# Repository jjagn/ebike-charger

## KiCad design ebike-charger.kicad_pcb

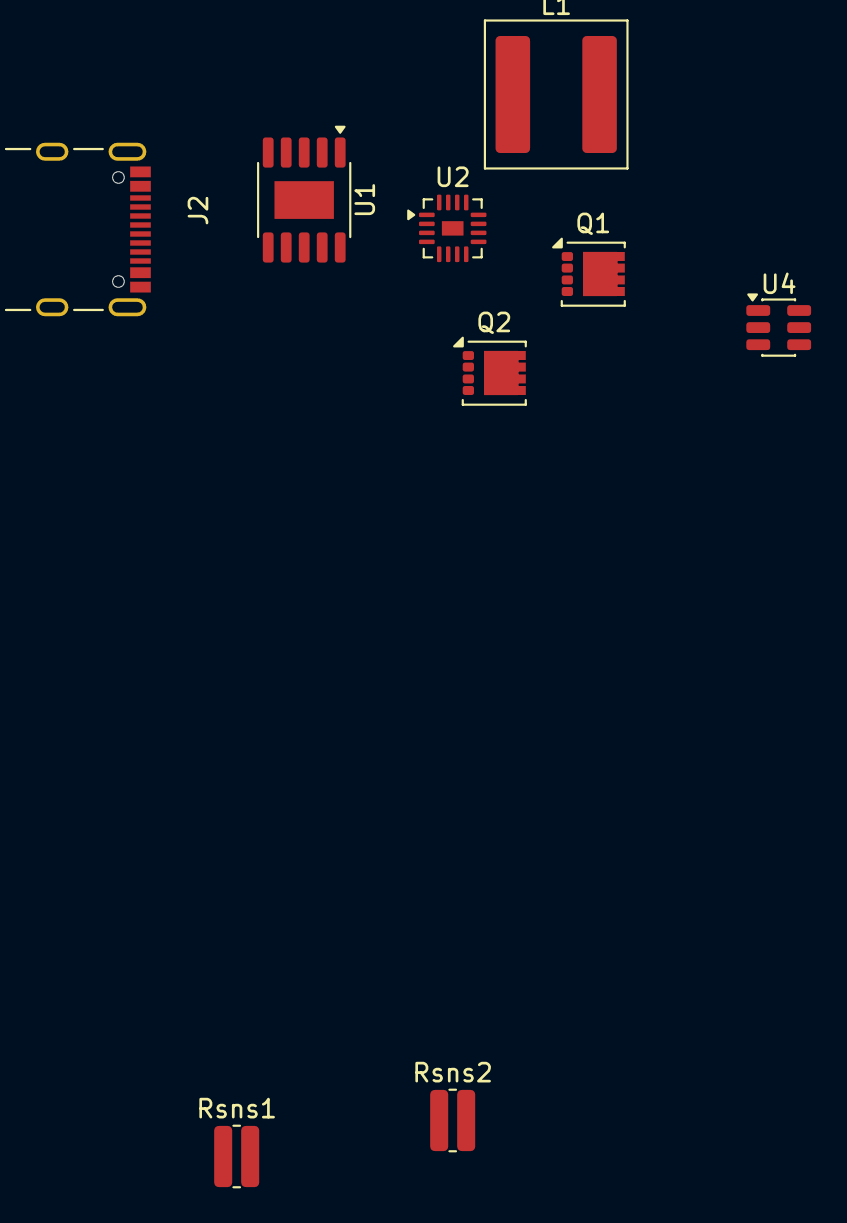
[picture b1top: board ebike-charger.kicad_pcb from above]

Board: 2 copper layers, 9 parts (0 on the bottom side), 12 nets, no tracks yet.

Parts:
J2: UJ20-C-H-G-SMT-2A-P16-TR; SAMESKY_UJ20-C-H-G-SMT-2A-P16-TR
L1: 8.2uH/14.5mR; L_Coilcraft_XAL7070-XXX
Q1, Q2: CSD18543Q3A; VSON-8_3.3x3.3mm_P0.65mm_NexFET
Rsns1, Rsns2: 8mR; R_0612_1632Metric
U1: CH224K; SSOP-10-1EP_3.9x4.9mm_P1mm_EP2.1x3.3mm
U2: TPS43060RTER; Texas_RTE_WQFN-16-1EP_3x3mm_P0.5mm_EP1.2x0.8mm
U4: LM74700; SOT-23-6

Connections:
/Boost Converter/HDRV: Q2.4 (G), U2.13 (HDRV)
/Boost Converter/LDRV: Q1.4 (G), U2.8 (LDRV)
/Boost Converter/SW: L1.2, Q1.5 (D), Q2.1 (S), Q2.2 (S), Q2.3 (S), U2.12 (SW)
/Boost Converter/V_CHARGE: Q2.5 (D), U4.3 (EN), U4.6 (ANODE)
/USB-C Input/CC1: J2.A5 (CC1), U1.7 (CC1)
/USB-C Input/CC2: J2.B5 (CC2), U1.6 (CC2)
/USB-C Input/D+: J2.A6 (DP1), J2.B6 (DP2), U1.4 (DP)
/USB-C Input/D-: J2.A7 (DN1), J2.B7 (DN2), U1.5 (DM)
/USB-C Input/VDD: U1.1 (VDD), U1.2 (CFG2)
GND: J2.A1_B12 (GND), J2.B1_A12 (GND), J2.SH1 (SHIELD), J2.SH2 (SHIELD), J2.SH3 (SHIELD), J2.SH4 (SHIELD), Q1.1 (S), Q1.2 (S), Q1.3 (S), U1.3 (CFG3), U1.9 (CFG1), U1.11 (GND), U2.9 (PGND), U2.16 (AGND_16), U2.17 (AGND_17), U4.2 (GND)
unnamed: L1.1, Rsns1.2, Rsns2.2
VBUS: J2.A4_B9 (VBUS), J2.B4_A9 (VBUS), Rsns1.1, Rsns2.1, U2.7 (VIN)

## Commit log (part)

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2026-06-27 uploading
2026-06-27 syncing
2026-06-27 added boost converter schematic
